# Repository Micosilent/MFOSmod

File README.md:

# MFOSmod

This is a collection of modules from Ray Wilson's [Music From Outer Space](http://musicfromouterspace.com/).

I will be using SMT in all the places I can, and replacing obsolete components that cant be found in the usual electronic distributors ( mouser or digikey ), with appropiate ones, following if possible Ray Wilson's advice on parts.

---

## MFOS SUPER-Modular Bundle

The idea is to end with all the modules from the supermodular bundle for starters, once we have all this modules we can look into transcripting other modules.

TODO:
- [x] 1. VCO
- [ ] 2. State Variable 12dB/Oct VCF
- [ ] 3. ADSR Envelope Generator
- [ ] 4. Mini-Controller
- [ ] 5. Dual Log/lin VCA
- [ ] 6. VC Low Frequency Oscillator
- [ ] 7. Dual AR Envelope Generator
- [ ] 8. Noise Cornucopia
- [ ] 9. Four Channel Stereo Panning Mixer
- [ ] 10. Delayed Modulation Module
- [ ] 11. Sample & Hold
- [ ] 12. Sonic Multiplier
- [ ] 13. Low Pass 24db/OCT VCF
- [ ] 14. Wave Freaker
- [ ] 15. Stereo Auto-Panner
- [ ] 16. Multi-Function Module
- [ ] 17. MFOS 8 Stage Phase Shifter
- [ ] 18. MFOS Voltage Quantizer

You dont really need all this modules to make a working synthesizer, but I am planning to make all the modules in KiCAD and start bulding them progresivly.

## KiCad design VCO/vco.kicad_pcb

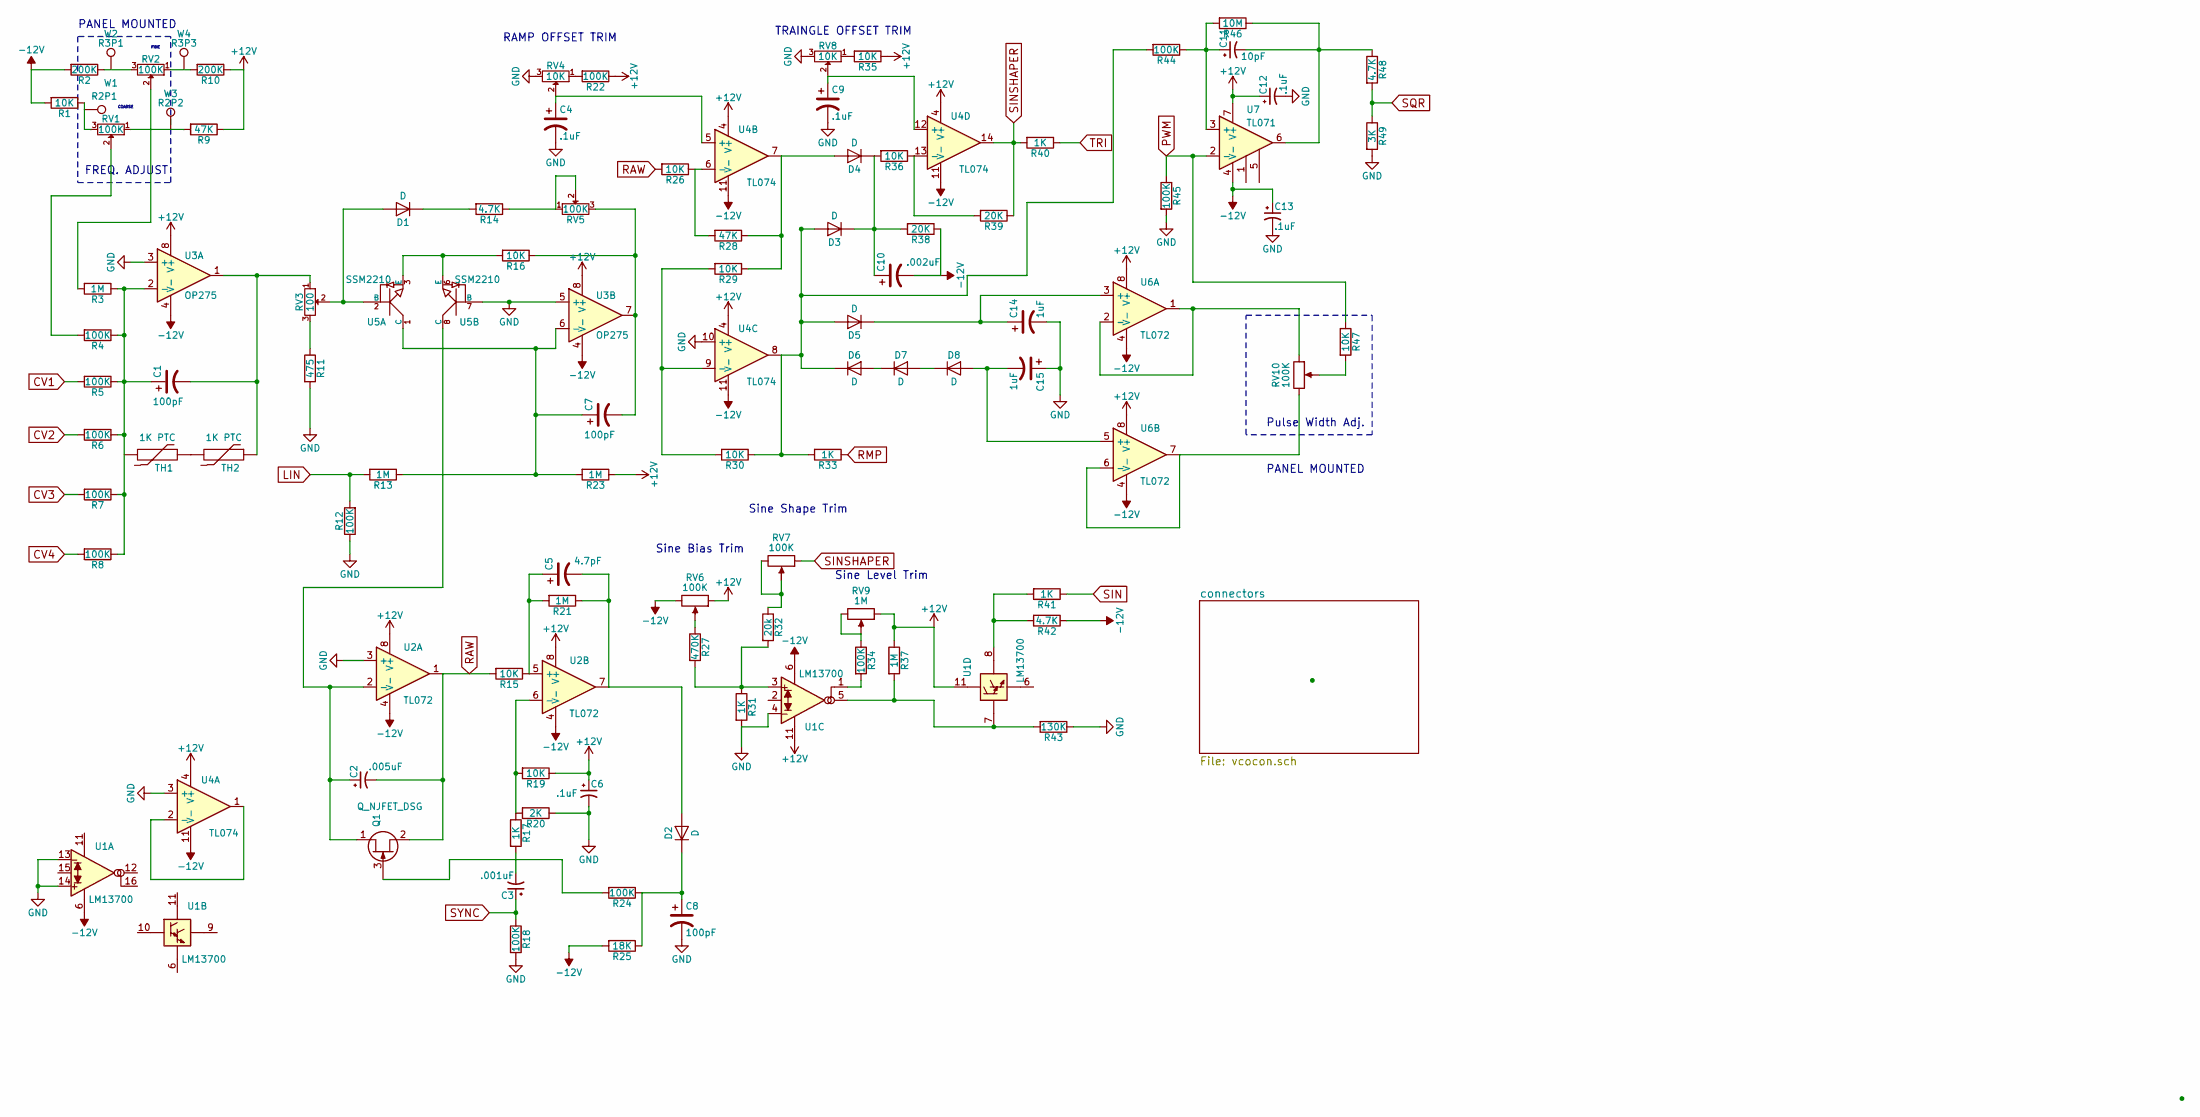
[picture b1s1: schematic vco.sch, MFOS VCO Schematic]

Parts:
C1, C7, C8: 100pF; C_0603
C2: .005uF; C_0805
C3: .001uF; C_0603
C4, C6, C9, C12, C13: .1uF; C_0805
C5: 4.7pF; C_0805
C10: .002uF; C_0805
C11: 10pF; C_0805
C14, C15: 1uF; C_0805
D1, D2, D3, D4, D5, D6, D7, D8: D; D_MiniMELF
Q1: Q_NJFET_DSG; SOT-23
R1, R15, R16, R19, R26, R29, R30, R35, R36, R47: 10K; R_0805
R2, R10: 200K; R_0805
R3, R13, R21, R23, R37: 1M; R_0805
R4, R5, R6, R7, R8, R12, R18, R22, R24, R34, R44, R45: 100K; R_0805
R9, R28: 47K; R_0805
R11: 475; R_0805
R14, R42, R48: 4.7K; R_0805
R17, R31, R33, R40, R41: 1K; R_0805
R20: 2K; R_0805
R25: 18K; R_0805
R27: 470K; R_0805
R32: 20k; R_0805
R38, R39: 20K; R_0805
R43: 130K; R_0805
R46: 10M; R_0805
R49: 3K; R_0805_HandSoldering
RV1, RV2, RV10: 100K; Potentiometer_Alps_RK09K_Horizontal
RV3: 100; Potentiometer_Trimmer-EVM3E
RV4, RV8: 10K; Potentiometer_Trimmer-EVM3E
RV5, RV6, RV7: 100K; Potentiometer_Trimmer-EVM3E
RV9: 1M; Potentiometer_Trimmer-EVM3E
TH1, TH2: 1K PTC; R_1206
U1: LM13700; SOIC-16_3.9x9.9mm_Pitch1.27mm
U2, U6: TL072; SOIC-8_3.9x4.9mm_Pitch1.27mm
U3: OP275; SOIC-8_3.9x4.9mm_Pitch1.27mm
U4: TL074; SOIC-14_3.9x8.7mm_Pitch1.27mm
U5: SSM2210; SOIC-8_3.9x4.9mm_Pitch1.27mm
U7: TL071; SOIC-8_3.9x4.9mm_Pitch1.27mm
W1: R2P1; SolderWirePad_single_2mmDrill
W2: R3P1; SolderWirePad_single_2mmDrill
W3: R2P2; SolderWirePad_single_2mmDrill
W4: R3P3; SolderWirePad_single_2mmDrill

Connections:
+12V: C6.1, C12.1, R9.1, R10.1, R19.1, R22.1, R23.1, R35.1, R37.1, RV6.1, RV9.1, U1.11 (V+), U2.8 (V+), U3.8 (V+), U4.4 (V+), U6.8 (V+), U7.7 (V+); also elsewhere on the board
-12V: C10.2, C13.1, R1.2, R2.2, R25.2, R38.1, R42.1, RV6.3, U1.6 (V-), U2.4 (V-), U3.4 (V-), U4.11 (V-), U6.4 (V-), U7.4 (V-); also elsewhere on the board
CV1: R5.2; also elsewhere on the board
CV2: R6.2; also elsewhere on the board
CV3: R7.2; also elsewhere on the board
GND: C4.2, C6.2, C8.2, C9.2, C12.2, C13.2, C14.2, C15.1, R11.2, R12.1, R18.2, R20.1, R31.2, R43.1, R45.2, R49.2, RV4.3, RV8.3, U1.4 (INPUT(-)), U1.13 (INPUT(-)), U1.14 (INPUT(+)), U2.3 (+), U3.3 (+), U3.5 (+), U4.3 (+), U4.10 (+), U5.7 (B); also elsewhere on the board
LIN: R12.2, R13.2; also elsewhere on the board
unnamed: C1.1, R3.1, R4.1, R5.1, R6.1, R7.1, R8.1, U3.2 (-)
unnamed: C1.2, RV3.1, TH2.1, U3.1
unnamed: C2.1, Q1.1 (D), U2.2 (-), U5.8 (C)
unnamed: C3.2, R17.2
unnamed: C4.1, RV4.2, U4.5 (+)
unnamed: C5.1, R15.1, R21.2, U2.5 (+)
unnamed: C5.2, D2.2 (A), R21.1, U2.7
unnamed: C7.1, R13.1, R23.2, U3.6 (-), U5.1 (C)
unnamed: C7.2, R16.1, RV5.3, U3.7
unnamed: C8.1, D2.1 (K), R24.1, R25.1
unnamed: C9.1, RV8.2, U4.12 (+)
unnamed: C10.1, D3.1 (K), D4.1 (K), R36.2, R38.2
unnamed: C11.1, R44.1, R46.2, U7.3 (+)
unnamed: C11.2, R46.1, R48.1, U7.6
unnamed: C14.1, D5.1 (K), U6.3 (+)
unnamed: C15.2, D8.2 (A), U6.5 (+)
unnamed: D1.1 (K), R14.2
unnamed: D1.2 (A), RV3.2, U5.2 (B)
unnamed: D3.2 (A), D5.2 (A), D6.1 (K), R30.1, R33.2, R44.2, U4.8
unnamed: D4.2 (A), R28.1, R29.1, U4.7
unnamed: D6.2 (A), D7.1 (K)
unnamed: D7.2 (A), D8.1 (K)
unnamed: Q1.3 (G), R24.2
unnamed: R1.1, RV1.3
unnamed: R2.1, RV2.3
unnamed: R3.2, RV2.2
unnamed: R4.2, RV1.2
unnamed: R9.2, RV1.1
unnamed: R10.2, RV2.1
unnamed: R11.1, RV3.3
unnamed: R14.1, RV5.1, RV5.2
unnamed: R16.2, U5.3 (E), U5.6 (E)
unnamed: R17.1, R19.2, R20.2, U2.6 (-)
unnamed: R22.2, RV4.1
unnamed: R26.1, R28.2, U4.6 (-)
unnamed: R27.1, RV6.2
unnamed: R27.2, R31.1, R32.2, U1.3 (INPUT(+))
unnamed: R29.2, R30.2, U4.9 (-)
unnamed: R32.1, RV7.2, RV7.3
unnamed: R34.1, RV9.2, RV9.3
unnamed: R34.2, U1.1 (AMP_BIAS_INPUT)
unnamed: R35.2, RV8.1
unnamed: R36.1, R39.2, U4.13 (-)
unnamed: R37.2, R43.2, U1.5 (OUTPUT), U1.7 (BUFFER_INPUT)
unnamed: R41.2, R42.2, U1.8 (BUFFER_OUTPUT)
unnamed: R47.2, RV10.2
unnamed: RV10.1, U6.1, U6.2 (-)
unnamed: RV10.3, U6.6 (-), U6.7
unnamed: TH1.1, TH2.2
unnamed: U4.1, U4.2 (-)
PWM: R45.1, R47.1, U7.2 (-); also elsewhere on the board
RAW: C2.2, Q1.2 (S), R15.2, R26.2, U2.1
RMP: R33.1; also elsewhere on the board
SIN: R41.1; also elsewhere on the board
SINSHAPER: R39.1, R40.2, RV7.1, U4.14
SQR: R48.2, R49.1; also elsewhere on the board
SYNC: C3.1, R18.1; also elsewhere on the board
TRI: R40.1; also elsewhere on the board

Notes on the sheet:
FREQ. ADJUST
COARSE
FINE
RAMP OFFSET TRIM
TRAINGLE OFFSET TRIM
Sine Bias Trim
Sine Shape Trim
Sine Level Trim
Pulse Width Adj.
PANEL MOUNTED

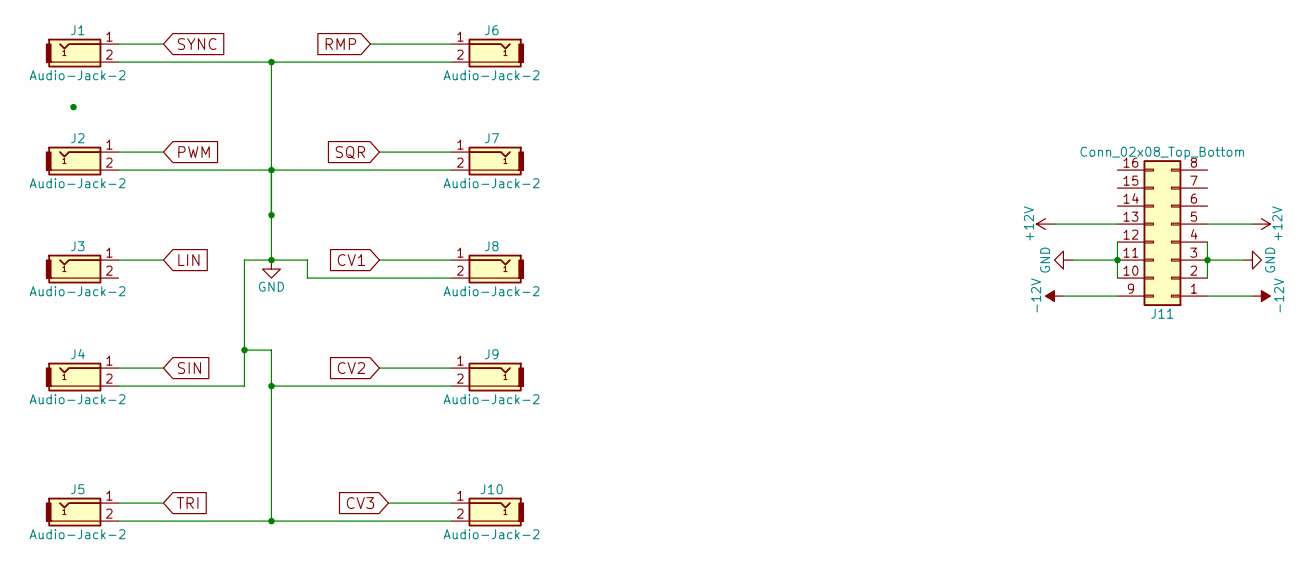
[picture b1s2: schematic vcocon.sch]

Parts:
J1, J2, J3, J4, J5, J6, J7, J8, J9, J10: Audio-Jack-2; audio_jack_3.5mm_schurter
J11: Conn_02x08_Top_Bottom; Molex_NanoFit_2x08x2.50mm_Straight

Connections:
+12V: J11.5, J11.13; also elsewhere on the board
-12V: J11.1, J11.9; also elsewhere on the board
CV1: J8.1; also elsewhere on the board
CV2: J9.1; also elsewhere on the board
CV3: J10.1; also elsewhere on the board
GND: J1.2, J2.2, J4.2, J5.2, J6.2, J7.2, J8.2, J9.2, J10.2, J11.2, J11.3, J11.4, J11.10, J11.11, J11.12; also elsewhere on the board
LIN: J3.1; also elsewhere on the board
PWM: J2.1; also elsewhere on the board
RMP: J6.1; also elsewhere on the board
SIN: J4.1; also elsewhere on the board
SQR: J7.1; also elsewhere on the board
SYNC: J1.1; also elsewhere on the board
TRI: J5.1; also elsewhere on the board

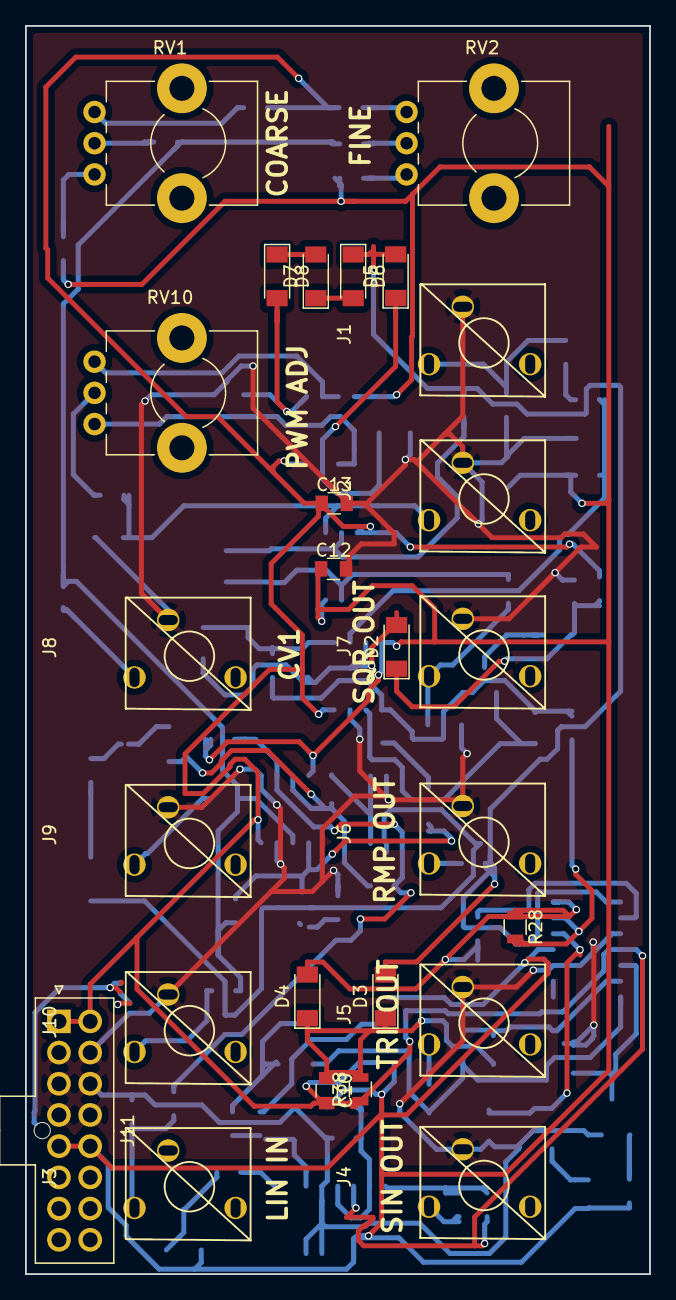
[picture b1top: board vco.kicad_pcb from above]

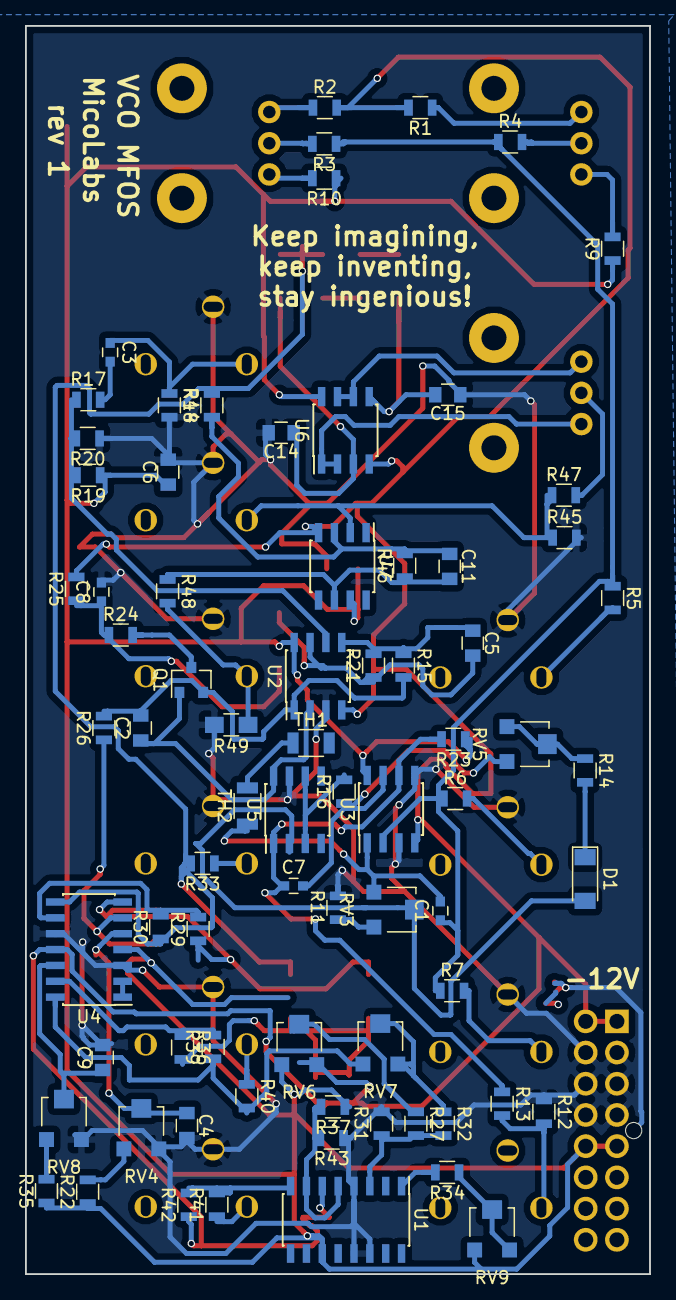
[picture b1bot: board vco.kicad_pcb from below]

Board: 2 copper layers, 50.0 x 100.0 mm, 102 parts (76 on the bottom side), 65 nets.

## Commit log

2018-01-23 Initial README
2018-01-23 VCO core schematic
    Starting up with the essential module, the VCO. The waveshaping part of the schematic is still missing, along with the PCB files
2018-02-11 VCO update
    vco pcb, gerbers and bom updated
2018-02-11 Drill File
    Forgot to add the drill file to the gerbres
2018-02-15 Missing SilkScreen
    Added missing files for fabrication
2018-03-01 Changed Readme
    Added all the wanted modules, for contributors to pick wich one they want to do
2018-03-01 Fixed README
    task list not formated properly
2018-03-01 Readme
    again.
2018-03-01 Initial Schematic Capture
    Missing Front Panel pots and bypasscaps
2018-03-02 Schematic Capture of ADSR Env.
    Missing EURORACK connector and SMD and THT layout
2018-03-02 Update LICENSE.md
    Updated LICENSE from MIT to CC-4 Non Comercial Share Alike
2018-03-12 test 1 VCF
2018-03-12 Changed Pot
    Trimmer potentiometer was too expensive, updated pcb and gerbers for cheaper trimmer pot
2018-03-12 Whops!
    Deleted aditional files
